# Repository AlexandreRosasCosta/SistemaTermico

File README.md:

# 💡 Dimmer de Cargas AC com ESP32 (Monitoramento via Serial + InfluxDB)

Este projeto implementa um dimmer de controle de fase para cargas AC (resistivas) usando um ESP32. O controle de potência e a leitura de temperatura são realizados pelo firmware do ESP32, e os dados de monitoramento são enviados pela porta **Serial/USB**.

Os dados da Serial são destinados a serem consumidos por um **serviço de ponte externo** que, por sua vez, os insere no banco de dados de séries temporais **InfluxDB** para monitoramento e visualização.

---

## 🛠️ Hardware e Configuração

### 1. Componentes Principais

| Componente | Função |
| :--- | :--- |
| **Microcontrolador** | ESP32-WROOM-32D |
| **Detector de Zero-Cross** | Módulo Zero-Cross (H11AA1 - U2 no esquema) |
| **Acionador de Potência** | Optotriac (MOC3023M - U4) + Triac (BTA16-600B - Q1) |
| **Sensor de Temperatura** | Termistor NTC de 10kΩ (TH2) |

### 2. Pinagem (Conforme o Esquema)

O firmware (`.ino`) e o esquema do KiCad definem a seguinte pinagem:

| Variável | Porta (Padrão) | Função no Circuito |
| :--- | :--- | :--- |
| `PIN_ZC` | `GPIO 27` | Entrada do detector de Zero-Cross (Interrupção) |
| `PIN_MOC` | `GPIO 26` | Saída para o Optotriac (Acionamento do Triac) |
| `PIN_TEMP` | `GPIO 34` | Entrada Analógica para o Termistor NTC |

---

## 💻 Ambiente de Monitoramento (InfluxDB)

O InfluxDB é utilizado para persistir e visualizar os dados de temperatura e os estados operacionais do dimmer.

### 1. Pré-requisitos

Certifique-se de ter instalado:

* **Docker**
* **Docker Compose**
* O **Serviço de Ponte Serial** (a ser desenvolvido/implementado separadamente, que lê o Serial do ESP32 e escreve no InfluxDB).

### 2. Configuração do Ambiente (`.env`)

Configure as variáveis de ambiente necessárias para o InfluxDB no arquivo **`.env`** (localmente, fora do Git):

| Variável | Exemplo de Valor | Descrição |
| :--- | :--- | :--- |
| `INFLUX_PORT` | `8086` | Porta local para acesso ao InfluxDB (UI/API). |
| `INFLUX_TOKEN` | `token_secreto_para_api` | Token de API inicial (necessário para o seu serviço de ponte). |
| `INFLUX_BUCKET` | `dimmer_data` | Bucket (banco de dados) para os dados do dimmer. |
| `INFLUX_ORG` | `minha_org` | Organização inicial do InfluxDB. |
| (Outras) | ... | Outras variáveis de configuração do Docker. |

### 3. Inicialização do InfluxDB

Execute o container do InfluxDB usando o Docker Compose:

```bash
docker-compose up -d

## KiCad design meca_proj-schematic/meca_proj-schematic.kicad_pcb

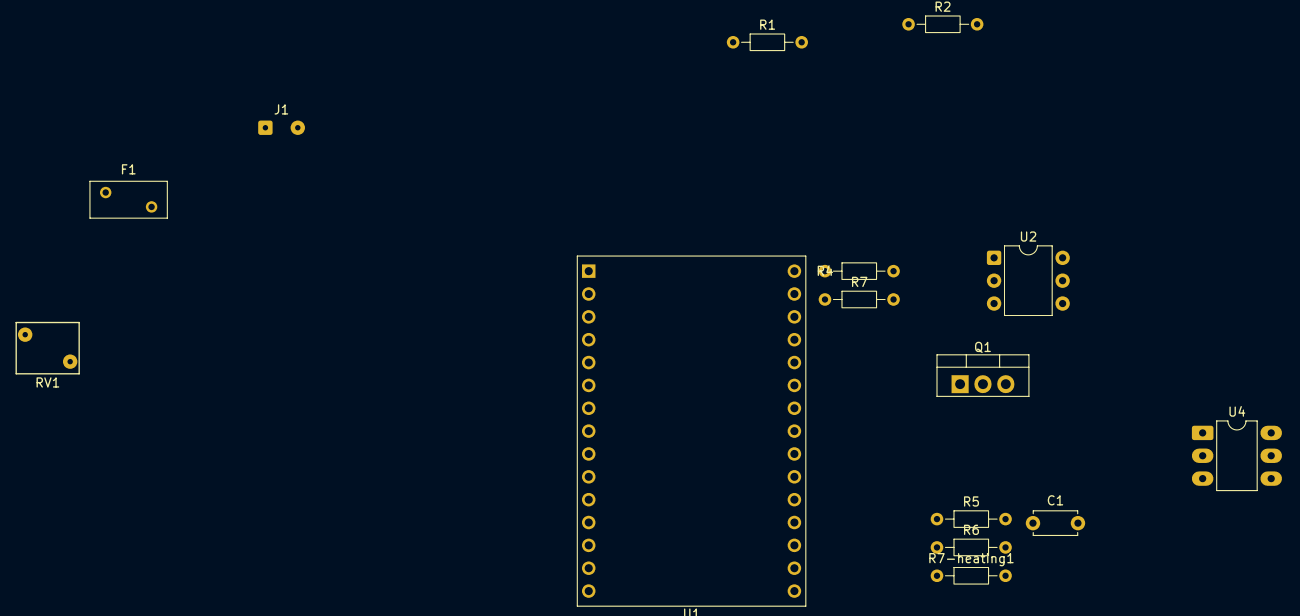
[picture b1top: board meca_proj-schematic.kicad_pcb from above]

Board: 2 copper layers, 15 parts (0 on the bottom side), 12 nets, no tracks yet.

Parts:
C1: C; C_Disc_D4.7mm_W2.5mm_P5.00mm
F1: Fuse; Fuse_BelFuse_0ZRE0005FF_L8.3mm_W3.8mm
J1: Conn_01x02_Pin; SolderWire-0.1sqmm_1x02_P3.6mm_D0.4mm_OD1mm
Q1: BTA16-600B; TO-220-3_Vertical
R1, R2: R; R_Axial_DIN0204_L3.6mm_D1.6mm_P7.62mm_Horizontal
R4: 10kR; R_Axial_DIN0204_L3.6mm_D1.6mm_P7.62mm_Horizontal
R5: 500R; R_Axial_DIN0204_L3.6mm_D1.6mm_P7.62mm_Horizontal
R6: 390kR; R_Axial_DIN0204_L3.6mm_D1.6mm_P7.62mm_Horizontal
R7: 1MR; R_Axial_DIN0204_L3.6mm_D1.6mm_P7.62mm_Horizontal
R7-heating1: 780kR; R_Axial_DIN0204_L3.6mm_D1.6mm_P7.62mm_Horizontal
RV1: Varistor; RV_Disc_D7mm_W5.7mm_P5mm
U1: ESP32-S2-WROVER; ESP32-C3-DevKitM-1
U2: H11AA1; DIP-6_W7.62mm
U4: MOC3023M; DIP-6_W7.62mm_LongPads

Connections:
/N: Q1.1 (A1), RV1.2, U2.2
GND: C1.2, R7.1, U1.1 (GND), U1.26 (GND), U2.4, U4.2
unnamed: C1.1, R2.2
unnamed: F1.2, R7-heating1.2, RV1.1, U2.1
unnamed: Q1.2 (A2), R6.1, R7-heating1.1
unnamed: Q1.3 (G), U4.4
unnamed: R1.2, R2.1
unnamed: R5.1, U4.1
unnamed: R6.2, U4.6
unnamed: R7.2, U2.6
unnamed: R1.1, R4.1, U1.2 (3V3)
unnamed: R4.2, U1.21 (IO18), U2.5

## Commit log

2025-12-08 feat: implement phase-control dimmer with NTC temperature reading and serial-based power adjustment
2025-12-13 chore: Ignore local environment variables (.env)
2025-12-13 docs: Add .env.example to document required environment variables
2025-12-13 feat: Add InfluxDB to docker-compose for time series persistence
2025-12-13 feat: Apply power curve (gamma) for smoother dimmer control
2025-12-13 Revise README for AC dimmer project with ESP32
    Updated project description and added hardware configuration details for the AC load dimmer using ESP32.
2025-12-21 Update .gitignore for PlatformIO, Python, logs and data files
2025-12-21 Organize firmware as PlatformIO project under firmware/
2025-12-21 Move Docker Compose file into infra/ directory
2025-12-21 Add analysis folder with Python scripts and raw InfluxDB CSVs
2025-12-21 Ignore Kate editor swap files
2025-12-21 Remove legacy root-level firmware and docker-compose files
2025-12-26 Feat: Added analysis scripts
2026-01-18 chore: remove obsolete Julia PI controller examples and results
2026-01-18 feat: add KiCad schematic and PCB project for thermal system
2026-01-18 feat: add interface module
2026-01-18 refactor: reorganize docker infrastructure
